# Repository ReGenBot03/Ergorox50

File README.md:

# ErgoRox50 - Split keyboard with joystick & Trackpad

### Schematic :

-------------

### Encloser :

-------------

### BOM :

|Item|Quantity|Link|
|-----------------------------------|-----------|-------------------------------------------------------------|
|minimal-fpc-i2c-pcb*|1|https://github.com/keyboard-magpie/minimal-fpc-i2c-pcb|
|Kailh Joystick|1|https://ko.aliexpress.com/item/32982601039.html|
|Joystick Cap (XBox 360)|1|https://ko.aliexpress.com/item/1005004579062558.html|
|TTC Hotswap Socket|52|https://ko.aliexpress.com/item/1005004922507959.html|
|SK6803 MINI-E 3MA|52|https://ko.aliexpress.com/item/1005003636565847.html|
|SOD123 Diode (1N4148W T4)|53|https://ko.aliexpress.com/item/32921490945.html|
|C Type Socket (Male & Female Set)|2|https://ko.aliexpress.com/item/1005005874481984.html|
|TRRS Socket|2|https://ko.aliexpress.com/item/32860019036.html|
|TRRS Cable|1|https://ko.aliexpress.com/item/1005005658312762.html|
|JST 2.0 PH Wire & Socket (6pin)|6||
|JST 2.0 PH Wire & Socket (2pin)|2||
|Cirque 40mm Curved Trackpad|1||
|FFC Cable (Forward, 0.5mm Pitch)|1|https://ko.aliexpress.com/item/1005006020830114.html|
|MX Switches + Keycaps|52||

##### *Strongly recommend that [minimal-fpc-i2c-pcb] order with assembly service (PCBA) 

##### Please understand that PCBs and enclosers are still in WIP state.
-------------

### Special Thanks to :

My friend Rox for awsome naming

elpekeñin from QMK Discord

pfn0 from QMK Discord

casuanoob from QMK Discord

..and all you guys who loves split keyboards!

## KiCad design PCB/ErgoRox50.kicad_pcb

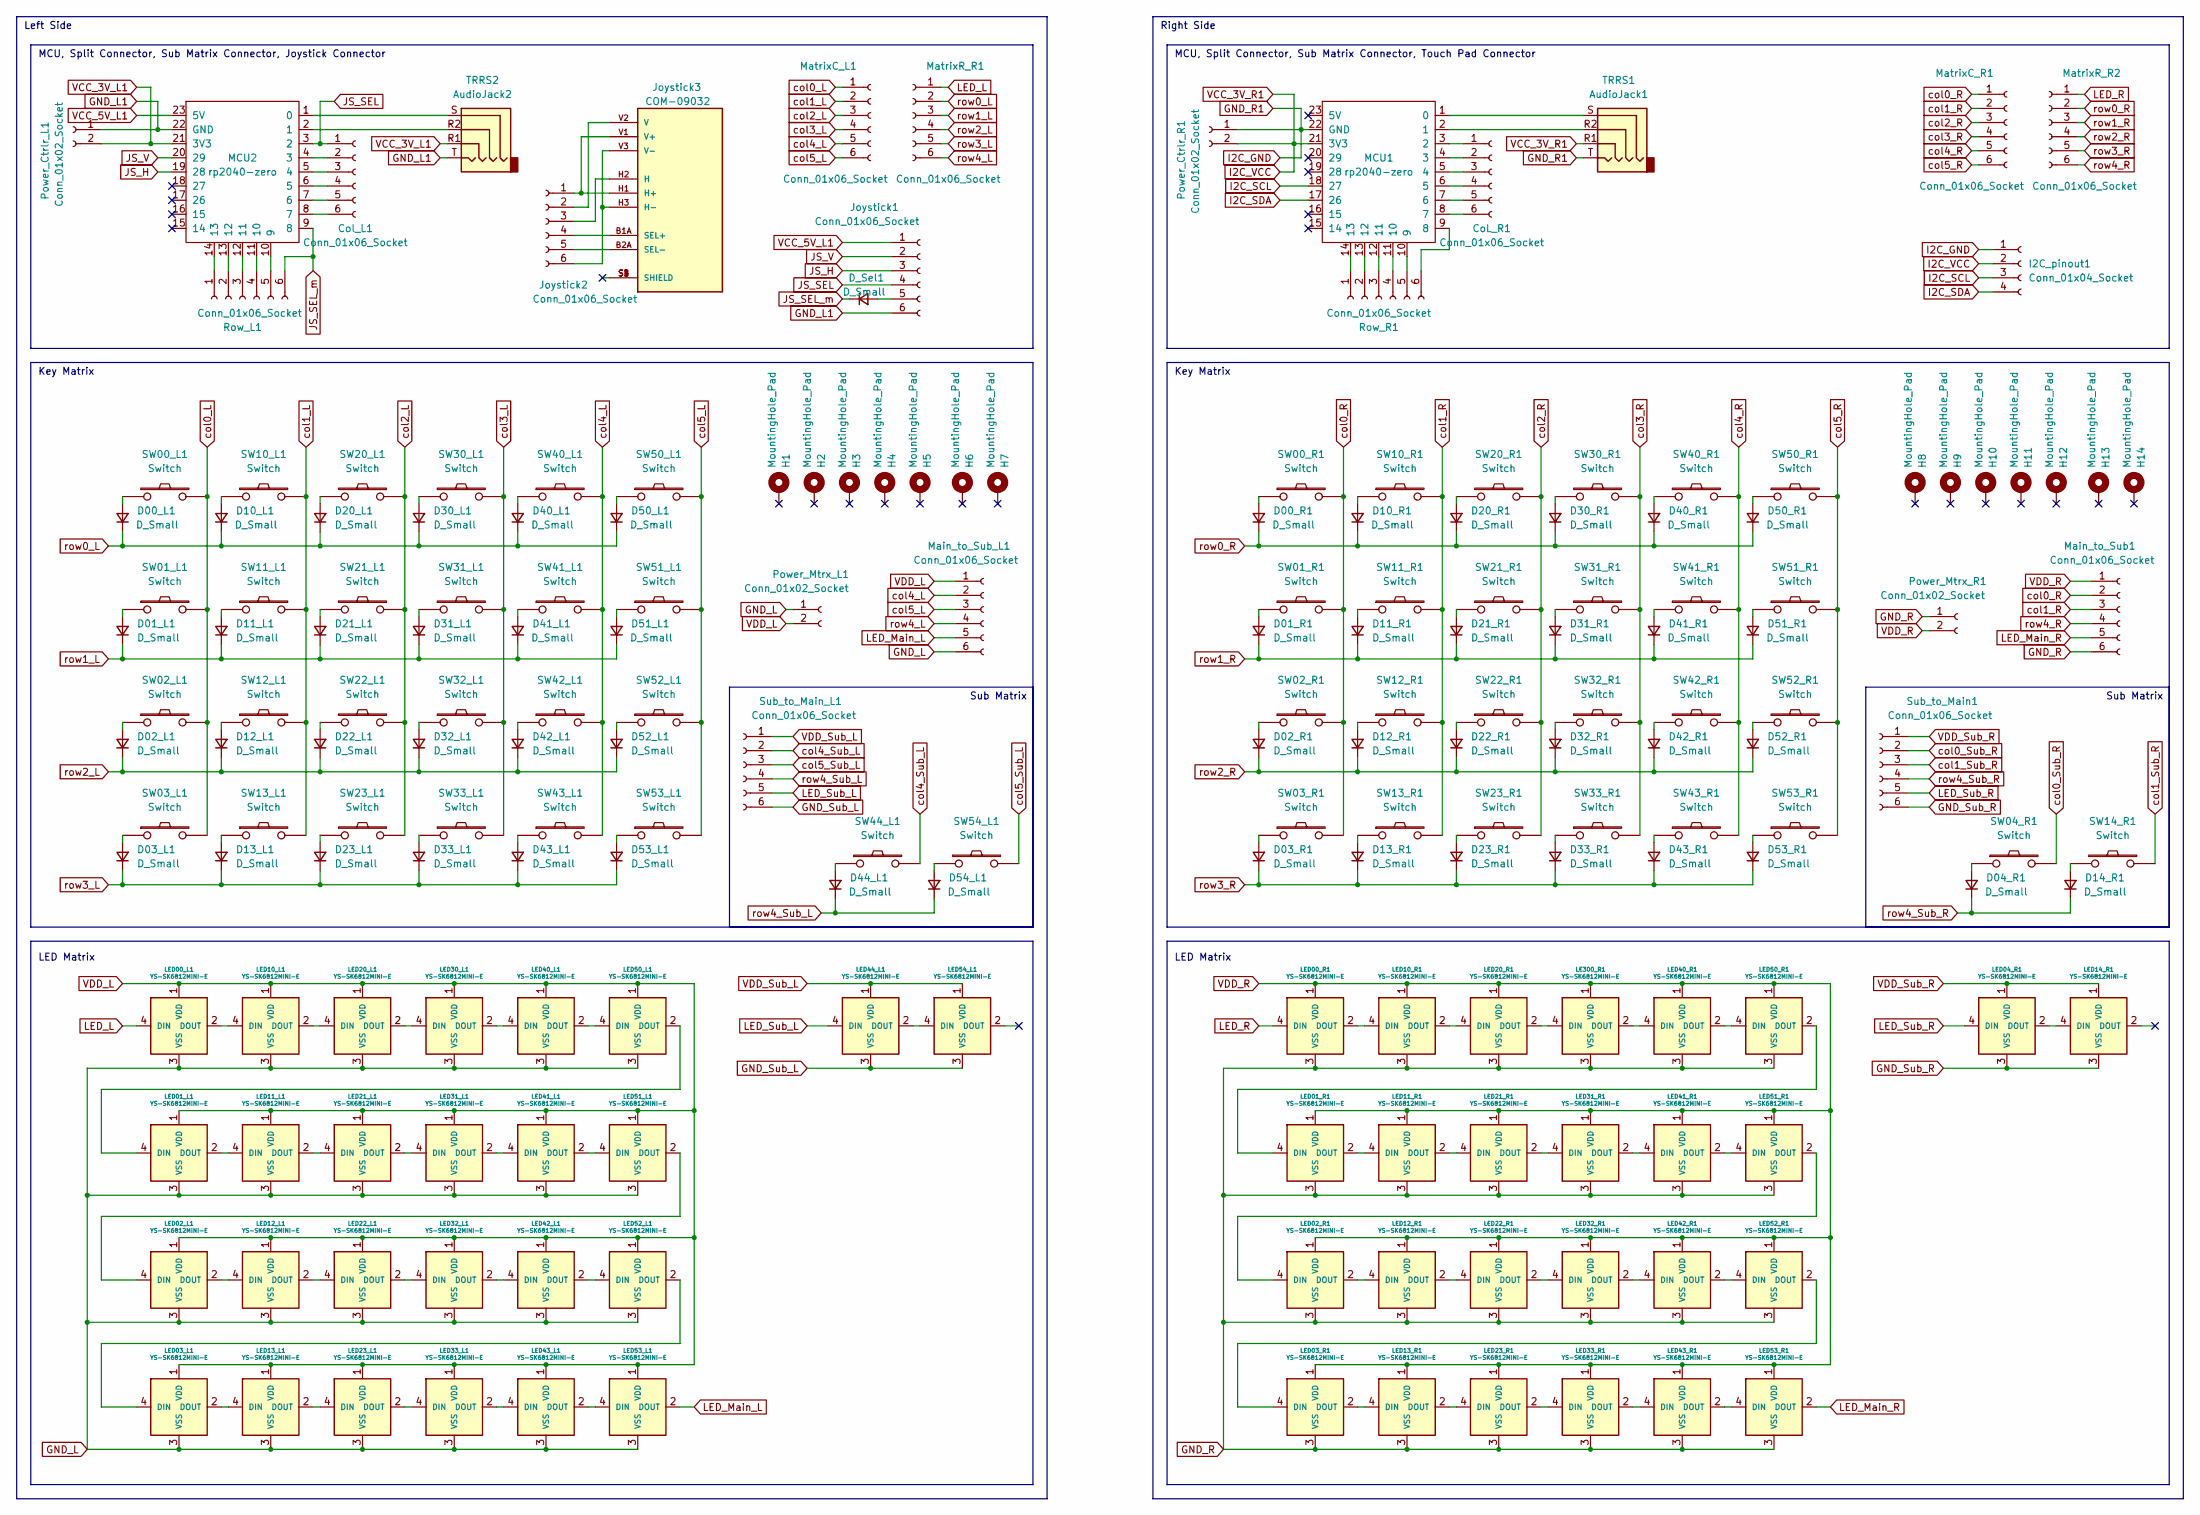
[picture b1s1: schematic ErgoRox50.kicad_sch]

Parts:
CoL_R1: Conn_01x06_Socket; PinHeader_1x06_P2.00mm_Vertical
Col_L1: Conn_01x06_Socket; PinHeader_1x06_P2.00mm_Vertical
D00_L1, D00_R1, D01_L1, D01_R1, D02_L1, D02_R1, D03_L1, D03_R1, D04_R1, D10_L1, D10_R1, D11_L1, D11_R1, D12_L1, D12_R1, D13_L1, D13_R1, D14_R1, D20_L1, D20_R1, D21_L1, D21_R1, D22_L1, D22_R1, D23_L1, D23_R1, D30_L1, D30_R1, D31_L1, D31_R1, D32_L1, D32_R1, D33_L1, D33_R1, D40_L1, D40_R1, D41_L1, D41_R1, D42_L1, D42_R1, D43_L1, D43_R1, D44_L1, D50_L1, D50_R1, D51_L1, D51_R1, D52_L1, D52_R1, D53_L1, D53_R1, D54_L1: D_Small; D_SOD123
D_Sel1: D_Small; D_SOD123
H1, H2, H3, H4, H5, H6, H7, H8, H9, H10, H11, H12, H13, H14: MountingHole_Pad; MountingHole_2.2mm_M2_DIN965
I2C_pinout1: Conn_01x04_Socket; PinHeader_1x04_P2.00mm_Vertical
Joystick1, Joystick2: Conn_01x06_Socket; PinHeader_1x06_P2.00mm_Vertical
Joystick3: COM-09032; XDCR_COM-09032; PARTREV N/A
LE300_R1: YS-SK6812MINI-E; SK6812-MINI-E
LED00_L1, LED00_R1, LED01_L1, LED01_R1, LED02_L1, LED02_R1, LED03_L1, LED03_R1, LED04_R1, LED10_L1, LED10_R1, LED11_L1, LED11_R1, LED12_L1, LED12_R1, LED13_L1, LED13_R1, LED14_R1, LED20_L1, LED20_R1, LED21_L1, LED21_R1, LED22_L1, LED22_R1, LED23_L1, LED23_R1, LED30_L1, LED31_L1, LED31_R1, LED32_L1, LED32_R1, LED33_L1, LED33_R1, LED40_L1, LED40_R1, LED41_L1, LED41_R1, LED42_L1, LED42_R1, LED43_L1, LED43_R1, LED44_L1, LED50_L1, LED50_R1, LED51_L1, LED51_R1, LED52_L1, LED52_R1, LED53_L1, LED53_R1, LED54_L1: YS-SK6812MINI-E; SK6812-MINI-E
MCU1, MCU2: rp2040-zero; rp2040-zero-tht-pads-cutout
Main_to_Sub1: Conn_01x06_Socket; PinHeader_1x06_P2.00mm_Vertical
Main_to_Sub_L1: Conn_01x06_Socket; PinHeader_1x06_P2.00mm_Vertical
MatrixC_L1: Conn_01x06_Socket; PinHeader_1x06_P2.00mm_Vertical
MatrixC_R1: Conn_01x06_Socket; PinHeader_1x06_P2.00mm_Vertical
MatrixR_R1, MatrixR_R2: Conn_01x06_Socket; PinHeader_1x06_P2.00mm_Vertical
Power_Ctrlr_L1: Conn_01x02_Socket; PinHeader_1x02_P2.00mm_Vertical
Power_Ctrlr_R1: Conn_01x02_Socket; PinHeader_1x02_P2.00mm_Vertical
Power_Mtrx_L1: Conn_01x02_Socket; PinHeader_1x02_P2.00mm_Vertical
Power_Mtrx_R1: Conn_01x02_Socket; PinHeader_1x02_P2.00mm_Vertical
Row_L1: Conn_01x06_Socket; PinHeader_1x06_P2.00mm_Vertical
Row_R1: Conn_01x06_Socket; PinHeader_1x06_P2.00mm_Vertical
SW00_L1, SW00_R1, SW01_L1, SW01_R1, SW02_L1, SW02_R1, SW03_L1, SW03_R1, SW04_R1, SW10_L1, SW10_R1, SW11_L1, SW11_R1, SW12_L1, SW12_R1, SW13_L1, SW13_R1, SW14_R1, SW20_L1, SW20_R1, SW21_L1, SW21_R1, SW22_L1, SW22_R1, SW23_L1, SW23_R1, SW30_L1, SW30_R1, SW31_L1, SW31_R1, SW32_L1, SW32_R1, SW33_L1, SW33_R1, SW40_L1, SW40_R1, SW41_L1, SW41_R1, SW42_L1, SW42_R1, SW43_L1, SW43_R1, SW44_L1, SW50_L1, SW50_R1, SW51_L1, SW51_R1, SW52_L1, SW52_R1, SW53_L1, SW53_R1, SW54_L1: Switch; Kailh_socket_MX
Sub_to_Main1: Conn_01x06_Socket; PinHeader_1x06_P2.00mm_Vertical
Sub_to_Main_L1: Conn_01x06_Socket; PinHeader_1x06_P2.00mm_Vertical
TRRS1: AudioJack1; TRRS-PJ-320A-no-Fmask
TRRS2: AudioJack2; TRRS-PJ-320A-no-Fmask

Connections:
GND_L: LED00_L1.3 (VSS), LED01_L1.3 (VSS), LED02_L1.3 (VSS), LED03_L1.3 (VSS), LED10_L1.3 (VSS), LED11_L1.3 (VSS), LED12_L1.3 (VSS), LED13_L1.3 (VSS), LED20_L1.3 (VSS), LED21_L1.3 (VSS), LED22_L1.3 (VSS), LED23_L1.3 (VSS), LED30_L1.3 (VSS), LED31_L1.3 (VSS), LED32_L1.3 (VSS), LED33_L1.3 (VSS), LED40_L1.3 (VSS), LED41_L1.3 (VSS), LED42_L1.3 (VSS), LED43_L1.3 (VSS), LED50_L1.3 (VSS), LED51_L1.3 (VSS), LED52_L1.3 (VSS), LED53_L1.3 (VSS), Main_to_Sub_L1.6, Power_Mtrx_L1.1
GND_L1: Joystick1.6, MCU2.22 (GND), Power_Ctrlr_L1.1, TRRS2.T
GND_R: LE300_R1.3 (VSS), LED00_R1.3 (VSS), LED01_R1.3 (VSS), LED02_R1.3 (VSS), LED03_R1.3 (VSS), LED10_R1.3 (VSS), LED11_R1.3 (VSS), LED12_R1.3 (VSS), LED13_R1.3 (VSS), LED20_R1.3 (VSS), LED21_R1.3 (VSS), LED22_R1.3 (VSS), LED23_R1.3 (VSS), LED31_R1.3 (VSS), LED32_R1.3 (VSS), LED33_R1.3 (VSS), LED40_R1.3 (VSS), LED41_R1.3 (VSS), LED42_R1.3 (VSS), LED43_R1.3 (VSS), LED50_R1.3 (VSS), LED51_R1.3 (VSS), LED52_R1.3 (VSS), LED53_R1.3 (VSS), Main_to_Sub1.6, Power_Mtrx_R1.1
GND_R1: I2C_pinout1.1, MCU1.22 (GND), Power_Ctrlr_R1.1, TRRS1.T
GND_Sub_L: LED44_L1.3 (VSS), LED54_L1.3 (VSS), Sub_to_Main_L1.6
GND_Sub_R: LED04_R1.3 (VSS), LED14_R1.3 (VSS), Sub_to_Main1.6
I2C_SCL: I2C_pinout1.3, MCU1.18 (27)
I2C_SDA: I2C_pinout1.4, MCU1.17 (26)
I2C_VCC: I2C_pinout1.2, MCU1.21 (3V3), Power_Ctrlr_R1.2, TRRS1.R1
JS_H: Joystick1.3, MCU2.19 (28)
JS_SEL: Col_L1.1, Joystick1.4, MCU2.3 (2)
JS_SEL_m: D_Sel1.1 (K), MCU2.9 (8), Row_L1.6
JS_V: Joystick1.2, MCU2.20 (29)
LED_L: LED00_L1.4 (DIN), MatrixR_R1.1
LED_Main_L: LED53_L1.2 (DOUT), Main_to_Sub_L1.5
LED_Main_R: LED53_R1.2 (DOUT), Main_to_Sub1.5
LED_R: LED00_R1.4 (DIN), MatrixR_R2.1
LED_Sub_L: LED44_L1.4 (DIN), Sub_to_Main_L1.5
LED_Sub_R: LED04_R1.4 (DIN), Sub_to_Main1.5
unnamed: CoL_R1.1, MCU1.3 (2)
unnamed: CoL_R1.2, MCU1.4 (3)
unnamed: CoL_R1.3, MCU1.5 (4)
unnamed: CoL_R1.4, MCU1.6 (5)
unnamed: CoL_R1.5, MCU1.7 (6)
unnamed: CoL_R1.6, MCU1.8 (7)
unnamed: Col_L1.2, MCU2.4 (3)
unnamed: Col_L1.3, MCU2.5 (4)
unnamed: Col_L1.4, MCU2.6 (5)
unnamed: Col_L1.5, MCU2.7 (6)
unnamed: Col_L1.6, MCU2.8 (7)
unnamed: D00_L1.2 (A), SW00_L1.1
unnamed: D00_R1.2 (A), SW00_R1.1
unnamed: D01_L1.2 (A), SW01_L1.1
unnamed: D01_R1.2 (A), SW01_R1.1
unnamed: D02_L1.2 (A), SW02_L1.1
unnamed: D02_R1.2 (A), SW02_R1.1
unnamed: D03_L1.2 (A), SW03_L1.1
unnamed: D03_R1.2 (A), SW03_R1.1
unnamed: D04_R1.2 (A), SW04_R1.1
unnamed: D10_L1.2 (A), SW10_L1.1
unnamed: D10_R1.2 (A), SW10_R1.1
unnamed: D11_L1.2 (A), SW11_L1.1
unnamed: D11_R1.2 (A), SW11_R1.1
unnamed: D12_L1.2 (A), SW12_L1.1
unnamed: D12_R1.2 (A), SW12_R1.1
unnamed: D13_L1.2 (A), SW13_L1.1
unnamed: D13_R1.2 (A), SW13_R1.1
unnamed: D14_R1.2 (A), SW14_R1.1
unnamed: D20_L1.2 (A), SW20_L1.1
unnamed: D20_R1.2 (A), SW20_R1.1
unnamed: D21_L1.2 (A), SW21_L1.1
unnamed: D21_R1.2 (A), SW21_R1.1
unnamed: D22_L1.2 (A), SW22_L1.1
unnamed: D22_R1.2 (A), SW22_R1.1
unnamed: D23_L1.2 (A), SW23_L1.1
unnamed: D23_R1.2 (A), SW23_R1.1
unnamed: D30_L1.2 (A), SW30_L1.1
unnamed: D30_R1.2 (A), SW30_R1.1
unnamed: D31_L1.2 (A), SW31_L1.1
unnamed: D31_R1.2 (A), SW31_R1.1
unnamed: D32_L1.2 (A), SW32_L1.1
unnamed: D32_R1.2 (A), SW32_R1.1
unnamed: D33_L1.2 (A), SW33_L1.1
unnamed: D33_R1.2 (A), SW33_R1.1
unnamed: D40_L1.2 (A), SW40_L1.1
unnamed: D40_R1.2 (A), SW40_R1.1
unnamed: D41_L1.2 (A), SW41_L1.1
unnamed: D41_R1.2 (A), SW41_R1.1
unnamed: D42_L1.2 (A), SW42_L1.1
unnamed: D42_R1.2 (A), SW42_R1.1
unnamed: D43_L1.2 (A), SW43_L1.1
unnamed: D43_R1.2 (A), SW43_R1.1
unnamed: D44_L1.2 (A), SW44_L1.1
unnamed: D50_L1.2 (A), SW50_L1.1
unnamed: D50_R1.2 (A), SW50_R1.1
unnamed: D51_L1.2 (A), SW51_L1.1
unnamed: D51_R1.2 (A), SW51_R1.1
unnamed: D52_L1.2 (A), SW52_L1.1
unnamed: D52_R1.2 (A), SW52_R1.1
unnamed: D53_L1.2 (A), SW53_L1.1
unnamed: D53_R1.2 (A), SW53_R1.1
unnamed: D54_L1.2 (A), SW54_L1.1
unnamed: D_Sel1.2 (A), Joystick1.5
unnamed: Joystick2.1, Joystick3.H1 (H+), Joystick3.V1 (V+)
unnamed: Joystick2.2, Joystick3.V2 (V)
unnamed: Joystick2.3, Joystick3.H2 (H)
unnamed: Joystick2.4, Joystick3.B1A (SEL+)
unnamed: Joystick2.5, Joystick3.B2A (SEL-)
unnamed: Joystick2.6, Joystick3.H3 (H-), Joystick3.V3 (V-)
unnamed: LE300_R1.4 (DIN), LED20_R1.2 (DOUT)
unnamed: LE300_R1.2 (DOUT), LED40_R1.4 (DIN)
unnamed: LED00_L1.2 (DOUT), LED10_L1.4 (DIN)
unnamed: LED00_R1.2 (DOUT), LED10_R1.4 (DIN)
unnamed: LED01_L1.4 (DIN), LED50_L1.2 (DOUT)
unnamed: LED01_L1.2 (DOUT), LED11_L1.4 (DIN)
unnamed: LED01_R1.4 (DIN), LED50_R1.2 (DOUT)
unnamed: LED01_R1.2 (DOUT), LED11_R1.4 (DIN)
unnamed: LED02_L1.4 (DIN), LED51_L1.2 (DOUT)
unnamed: LED02_L1.2 (DOUT), LED12_L1.4 (DIN)
unnamed: LED02_R1.4 (DIN), LED51_R1.2 (DOUT)
unnamed: LED02_R1.2 (DOUT), LED12_R1.4 (DIN)
unnamed: LED03_L1.4 (DIN), LED52_L1.2 (DOUT)
unnamed: LED03_L1.2 (DOUT), LED13_L1.4 (DIN)
unnamed: LED03_R1.4 (DIN), LED52_R1.2 (DOUT)
unnamed: LED03_R1.2 (DOUT), LED13_R1.4 (DIN)
unnamed: LED04_R1.2 (DOUT), LED14_R1.4 (DIN)
unnamed: LED10_L1.2 (DOUT), LED20_L1.4 (DIN)
unnamed: LED10_R1.2 (DOUT), LED20_R1.4 (DIN)
unnamed: LED11_L1.2 (DOUT), LED21_L1.4 (DIN)
unnamed: LED11_R1.2 (DOUT), LED21_R1.4 (DIN)
unnamed: LED12_L1.2 (DOUT), LED22_L1.4 (DIN)
unnamed: LED12_R1.2 (DOUT), LED22_R1.4 (DIN)
unnamed: LED13_L1.2 (DOUT), LED23_L1.4 (DIN)
unnamed: LED13_R1.2 (DOUT), LED23_R1.4 (DIN)
unnamed: LED20_L1.2 (DOUT), LED30_L1.4 (DIN)
unnamed: LED21_L1.2 (DOUT), LED31_L1.4 (DIN)
unnamed: LED21_R1.2 (DOUT), LED31_R1.4 (DIN)
unnamed: LED22_L1.2 (DOUT), LED32_L1.4 (DIN)
unnamed: LED22_R1.2 (DOUT), LED32_R1.4 (DIN)
unnamed: LED23_L1.2 (DOUT), LED33_L1.4 (DIN)
unnamed: LED23_R1.2 (DOUT), LED33_R1.4 (DIN)
unnamed: LED30_L1.2 (DOUT), LED40_L1.4 (DIN)
unnamed: LED31_L1.2 (DOUT), LED41_L1.4 (DIN)
unnamed: LED31_R1.2 (DOUT), LED41_R1.4 (DIN)
unnamed: LED32_L1.2 (DOUT), LED42_L1.4 (DIN)
unnamed: LED32_R1.2 (DOUT), LED42_R1.4 (DIN)
unnamed: LED33_L1.2 (DOUT), LED43_L1.4 (DIN)
unnamed: LED33_R1.2 (DOUT), LED43_R1.4 (DIN)
unnamed: LED40_L1.2 (DOUT), LED50_L1.4 (DIN)
unnamed: LED40_R1.2 (DOUT), LED50_R1.4 (DIN)
unnamed: LED41_L1.2 (DOUT), LED51_L1.4 (DIN)
unnamed: LED41_R1.2 (DOUT), LED51_R1.4 (DIN)
unnamed: LED42_L1.2 (DOUT), LED52_L1.4 (DIN)
unnamed: LED42_R1.2 (DOUT), LED52_R1.4 (DIN)
unnamed: LED43_L1.2 (DOUT), LED53_L1.4 (DIN)
unnamed: LED43_R1.2 (DOUT), LED53_R1.4 (DIN)
unnamed: LED44_L1.2 (DOUT), LED54_L1.4 (DIN)
unnamed: MCU1.1 (0), TRRS1.S
unnamed: MCU1.2 (1), TRRS1.R2
unnamed: MCU1.9 (8), Row_R1.6
unnamed: MCU1.10 (9), Row_R1.5
unnamed: MCU1.11 (10), Row_R1.4
unnamed: MCU1.12 (11), Row_R1.3
unnamed: MCU1.13 (12), Row_R1.2
unnamed: MCU1.14 (13), Row_R1.1
unnamed: MCU2.1 (0), TRRS2.S
unnamed: MCU2.2 (1), TRRS2.R2
unnamed: MCU2.10 (9), Row_L1.5
unnamed: MCU2.11 (10), Row_L1.4
unnamed: MCU2.12 (11), Row_L1.3
unnamed: MCU2.13 (12), Row_L1.2
unnamed: MCU2.14 (13), Row_L1.1
VCC_3V_L1: MCU2.21 (3V3), Power_Ctrlr_L1.2, TRRS2.R1
VCC_5V_L1: Joystick1.1, MCU2.23 (5V)
VDD_L: LED00_L1.1 (VDD), LED01_L1.1 (VDD), LED02_L1.1 (VDD), LED03_L1.1 (VDD), LED10_L1.1 (VDD), LED11_L1.1 (VDD), LED12_L1.1 (VDD), LED13_L1.1 (VDD), LED20_L1.1 (VDD), LED21_L1.1 (VDD), LED22_L1.1 (VDD), LED23_L1.1 (VDD), LED30_L1.1 (VDD), LED31_L1.1 (VDD), LED32_L1.1 (VDD), LED33_L1.1 (VDD), LED40_L1.1 (VDD), LED41_L1.1 (VDD), LED42_L1.1 (VDD), LED43_L1.1 (VDD), LED50_L1.1 (VDD), LED51_L1.1 (VDD), LED52_L1.1 (VDD), LED53_L1.1 (VDD), Main_to_Sub_L1.1, Power_Mtrx_L1.2
VDD_R: LE300_R1.1 (VDD), LED00_R1.1 (VDD), LED01_R1.1 (VDD), LED02_R1.1 (VDD), LED03_R1.1 (VDD), LED10_R1.1 (VDD), LED11_R1.1 (VDD), LED12_R1.1 (VDD), LED13_R1.1 (VDD), LED20_R1.1 (VDD), LED21_R1.1 (VDD), LED22_R1.1 (VDD), LED23_R1.1 (VDD), LED31_R1.1 (VDD), LED32_R1.1 (VDD), LED33_R1.1 (VDD), LED40_R1.1 (VDD), LED41_R1.1 (VDD), LED42_R1.1 (VDD), LED43_R1.1 (VDD), LED50_R1.1 (VDD), LED51_R1.1 (VDD), LED52_R1.1 (VDD), LED53_R1.1 (VDD), Main_to_Sub1.1, Power_Mtrx_R1.2
VDD_Sub_L: LED44_L1.1 (VDD), LED54_L1.1 (VDD), Sub_to_Main_L1.1
VDD_Sub_R: LED04_R1.1 (VDD), LED14_R1.1 (VDD), Sub_to_Main1.1
col0_L: MatrixC_L1.1, SW00_L1.2, SW01_L1.2, SW02_L1.2, SW03_L1.2
col0_R: Main_to_Sub1.2, MatrixC_R1.1, SW00_R1.2, SW01_R1.2, SW02_R1.2, SW03_R1.2
col0_Sub_R: SW04_R1.2, Sub_to_Main1.2
col1_L: MatrixC_L1.2, SW10_L1.2, SW11_L1.2, SW12_L1.2, SW13_L1.2
col1_R: Main_to_Sub1.3, MatrixC_R1.2, SW10_R1.2, SW11_R1.2, SW12_R1.2, SW13_R1.2
col1_Sub_R: SW14_R1.2, Sub_to_Main1.3
col2_L: MatrixC_L1.3, SW20_L1.2, SW21_L1.2, SW22_L1.2, SW23_L1.2
col2_R: MatrixC_R1.3, SW20_R1.2, SW21_R1.2, SW22_R1.2, SW23_R1.2
col3_L: MatrixC_L1.4, SW30_L1.2, SW31_L1.2, SW32_L1.2, SW33_L1.2
col3_R: MatrixC_R1.4, SW30_R1.2, SW31_R1.2, SW32_R1.2, SW33_R1.2
col4_L: Main_to_Sub_L1.2, MatrixC_L1.5, SW40_L1.2, SW41_L1.2, SW42_L1.2, SW43_L1.2
col4_R: MatrixC_R1.5, SW40_R1.2, SW41_R1.2, SW42_R1.2, SW43_R1.2
col4_Sub_L: SW44_L1.2, Sub_to_Main_L1.2
col5_L: Main_to_Sub_L1.3, MatrixC_L1.6, SW50_L1.2, SW51_L1.2, SW52_L1.2, SW53_L1.2
col5_R: MatrixC_R1.6, SW50_R1.2, SW51_R1.2, SW52_R1.2, SW53_R1.2
col5_Sub_L: SW54_L1.2, Sub_to_Main_L1.3
row0_L: D00_L1.1 (K), D10_L1.1 (K), D20_L1.1 (K), D30_L1.1 (K), D40_L1.1 (K), D50_L1.1 (K), MatrixR_R1.2
row0_R: D00_R1.1 (K), D10_R1.1 (K), D20_R1.1 (K), D30_R1.1 (K), D40_R1.1 (K), D50_R1.1 (K), MatrixR_R2.2
row1_L: D01_L1.1 (K), D11_L1.1 (K), D21_L1.1 (K), D31_L1.1 (K), D41_L1.1 (K), D51_L1.1 (K), MatrixR_R1.3
row1_R: D01_R1.1 (K), D11_R1.1 (K), D21_R1.1 (K), D31_R1.1 (K), D41_R1.1 (K), D51_R1.1 (K), MatrixR_R2.3
row2_L: D02_L1.1 (K), D12_L1.1 (K), D22_L1.1 (K), D32_L1.1 (K), D42_L1.1 (K), D52_L1.1 (K), MatrixR_R1.4
row2_R: D02_R1.1 (K), D12_R1.1 (K), D22_R1.1 (K), D32_R1.1 (K), D42_R1.1 (K), D52_R1.1 (K), MatrixR_R2.4
row3_L: D03_L1.1 (K), D13_L1.1 (K), D23_L1.1 (K), D33_L1.1 (K), D43_L1.1 (K), D53_L1.1 (K), MatrixR_R1.5
row3_R: D03_R1.1 (K), D13_R1.1 (K), D23_R1.1 (K), D33_R1.1 (K), D43_R1.1 (K), D53_R1.1 (K), MatrixR_R2.5
row4_L: Main_to_Sub_L1.4, MatrixR_R1.6
row4_R: Main_to_Sub1.4, MatrixR_R2.6
row4_Sub_L: D44_L1.1 (K), D54_L1.1 (K), Sub_to_Main_L1.4
row4_Sub_R: D04_R1.1 (K), D14_R1.1 (K), Sub_to_Main1.4

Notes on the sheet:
Sub Matrix
Right Side
LED Matrix
Left Side
MCU, Split Connector, Sub Matrix Connector, Joystick Connector
Key Matrix
MCU, Split Connector, Sub Matrix Connector, Touch Pad Connector

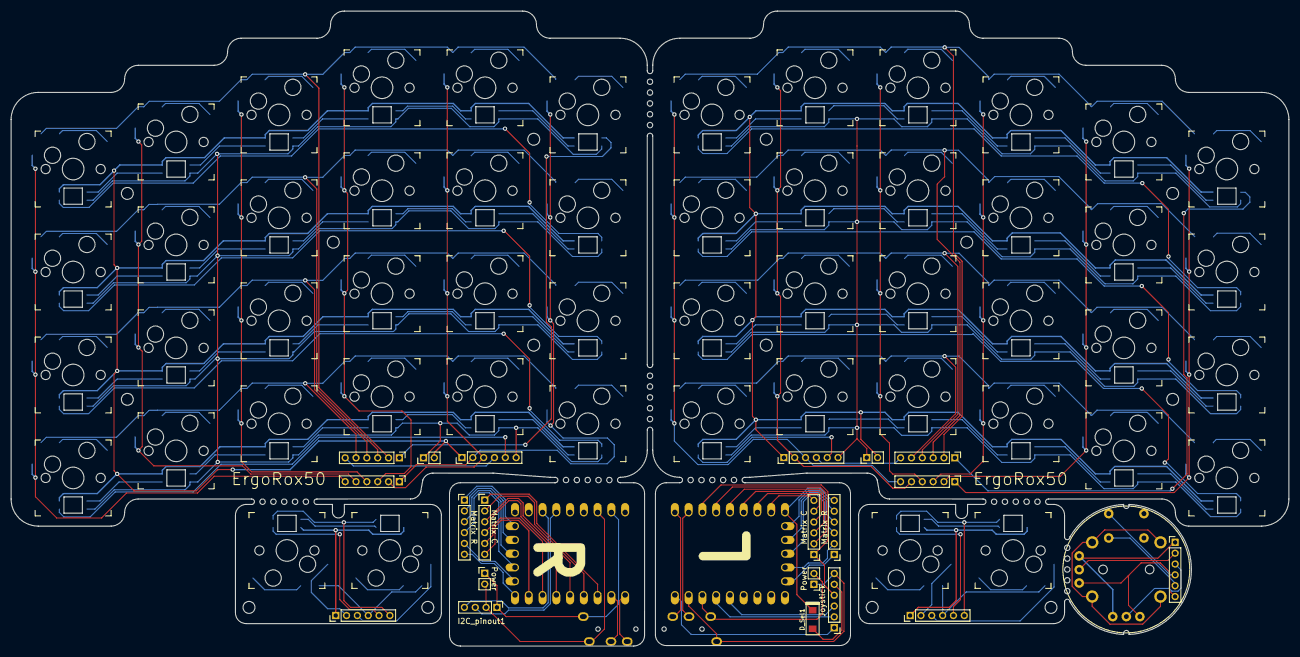
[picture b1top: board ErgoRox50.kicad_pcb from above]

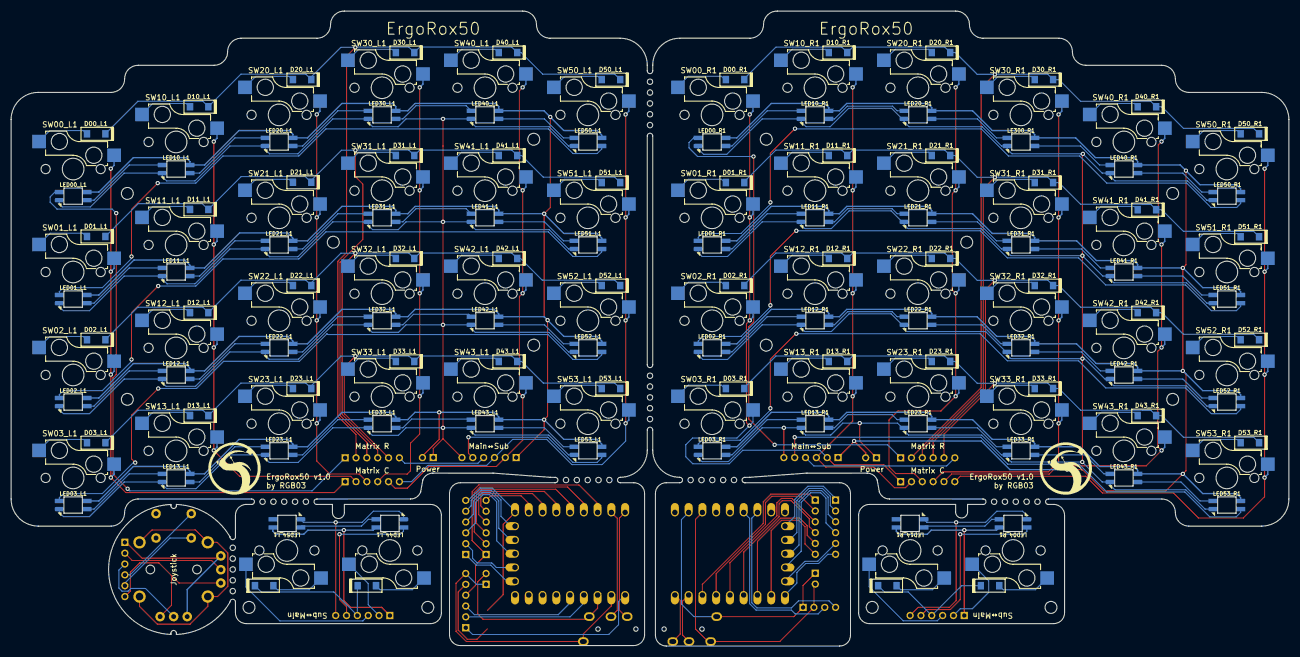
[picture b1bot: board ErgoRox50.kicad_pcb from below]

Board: 2 copper layers, 235.8 x 117.2 mm, 197 parts (106 on the bottom side), 186 nets.

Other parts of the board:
ProjectOrtholi: LOGO; Ortholi_logo_mini
ProjectOrtholi#2: LOGO; Ortholi_logo_mini

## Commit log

2024-01-30 Rename image.png to Schematics.png
